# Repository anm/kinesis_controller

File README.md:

# River's Kinesis Advantage Blackpill based controller board

This is a replacement controller board for the Kinesis Advantage keyboard.
It is a development of the kinBP by https://github.com/DmNosachev.

Changes from that one:
- Added piezo sounder, allowing for key clicks / beepy tunes.
- Added connector for the original Kinesis cable. There is no need to buy extra USB cables and hack up the case!
- Removed some unneeded connectors, that were for a custom thumb board I'm not using.
- Aligned thumb connector holes properly so you can use the original cable.
- Completely rerouted.
- N.B.: The pins used for the matrix are different - you must use the correct QMK configuration, also provided on my github.

## Build Notes

- There are two options for orientation of the function key connectors. Test it works before soldering in.
- Obtain qmk keyboard files from https://github.com/anm/qmk_firmware/ river branch.
- Build QMK with `qmk flash -kb kinesis/river -km river`.
- Flash with dfu-util
- Flash: Enter bootloader by holding BOOT0 button while resetting / powering on the board, then
  `dfu-util -a 0 -d 0483:df11 -s 0x8000000:leave -D kinesis_river_blackpill411_river.bin`.
  After flashing, you can also enter the bootloader by holding both shift keys and B on the keyboard.

More info at the parent project: https://github.com/DmNosachev/kinbp

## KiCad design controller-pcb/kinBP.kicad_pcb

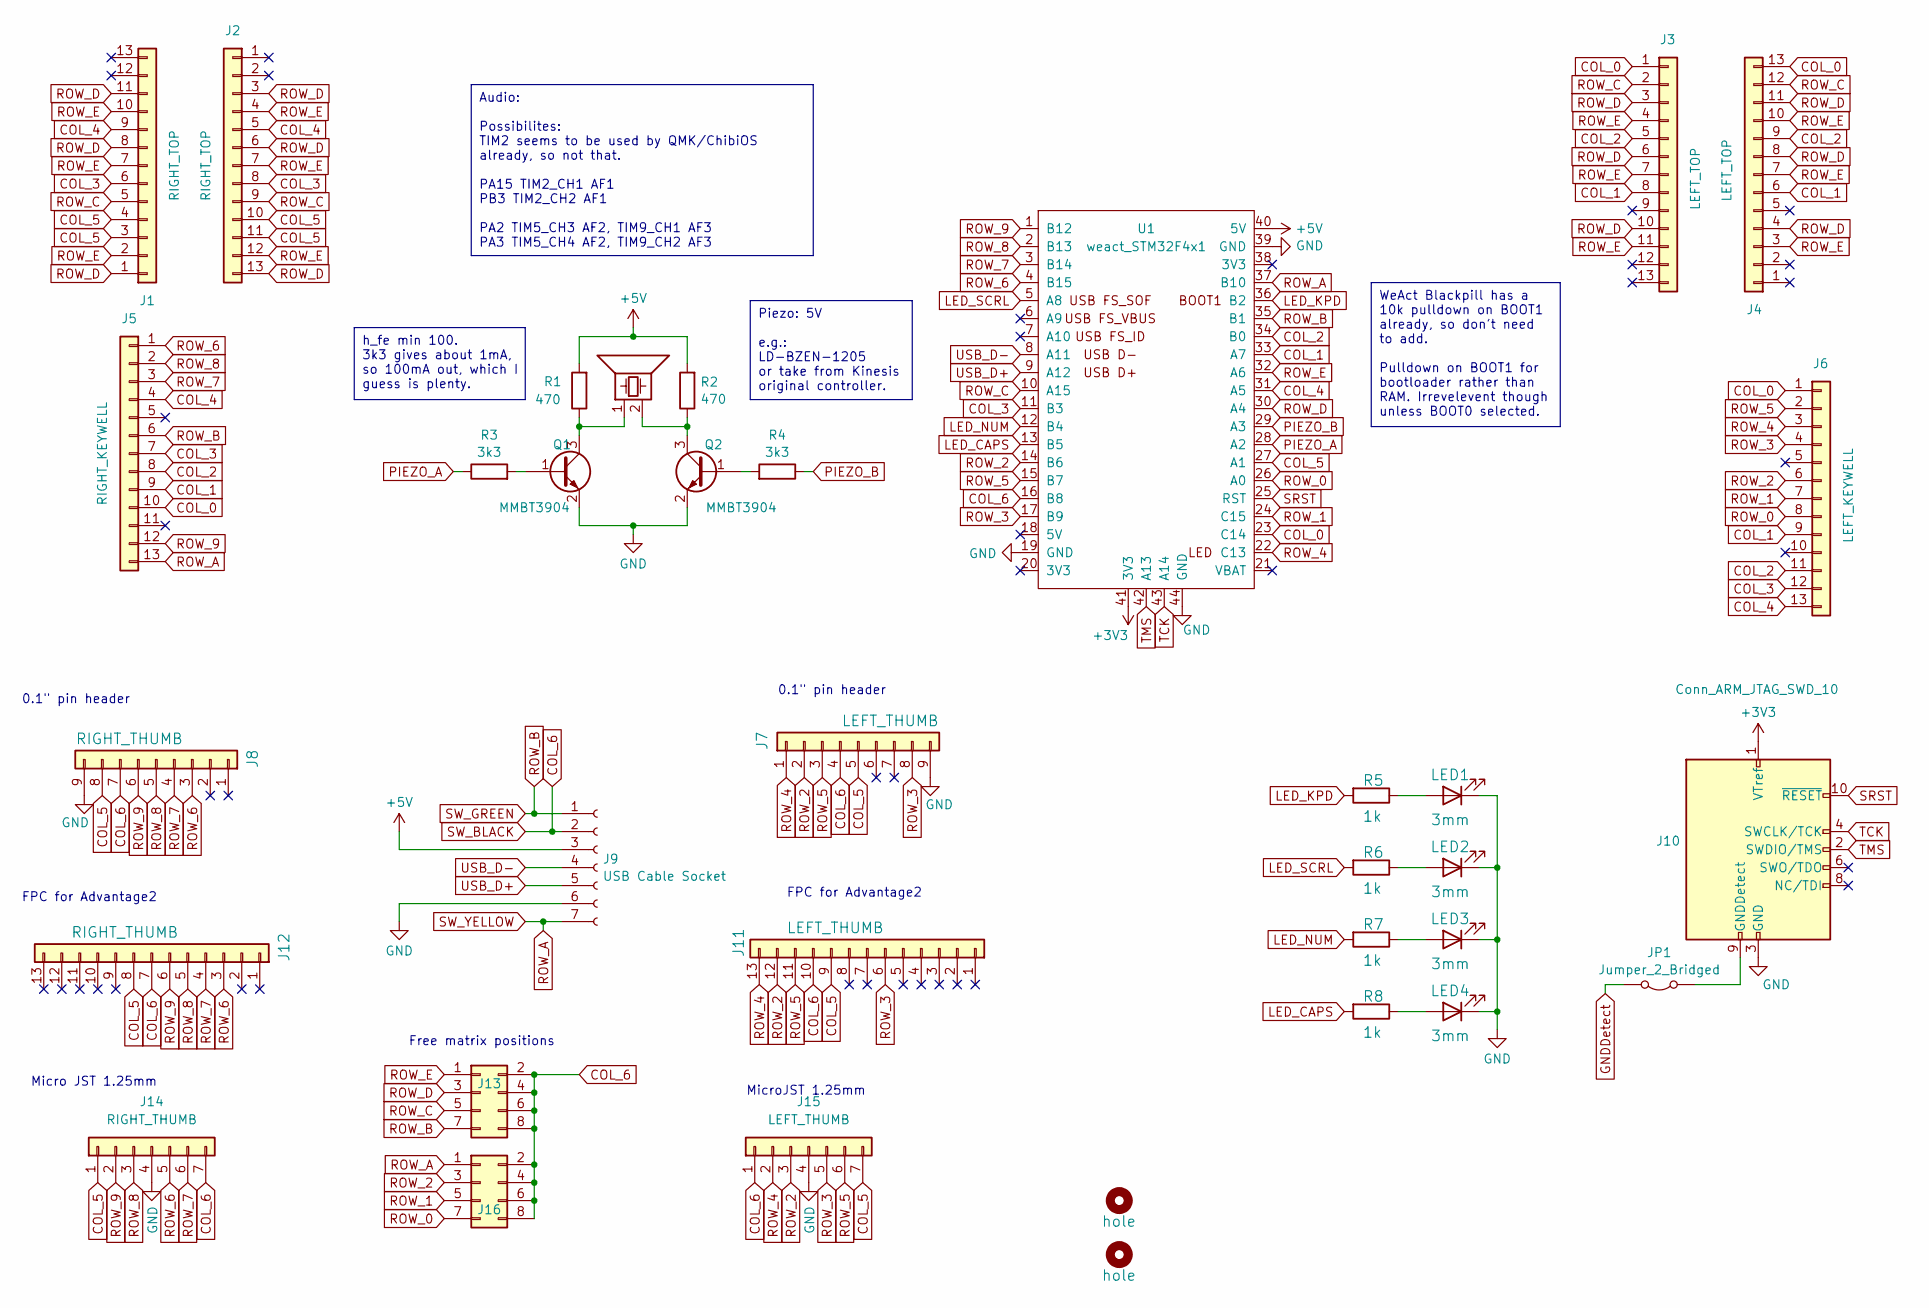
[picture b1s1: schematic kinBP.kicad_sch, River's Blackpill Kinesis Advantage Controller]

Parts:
H1: hole; MountingHole_4.3mm_M4_No_Copper
H2: hole; MountingHole_6mm
J1, J2: RIGHT_TOP; 39-53-2135
J3, J4: LEFT_TOP; 39-53-2135
J5: RIGHT_KEYWELL; 39-53-2135
J6: LEFT_KEYWELL; 39-53-2135
J7: LEFT_THUMB; PinHeader_1x09_P2.54mm_Vertical
J8: RIGHT_THUMB; PinHeader_1x09_P2.54mm_Vertical
J9: USB Cable Socket; JST_PH_B7B-PH-K_1x07_P2.00mm_Vertical
J10: Conn_ARM_JTAG_SWD_10; CONN_3220-10-0100-00_CNC; Digikey 1175-1627-ND
J11: LEFT_THUMB; 39-53-2135
J12: RIGHT_THUMB; 39-53-2135
J13, J16: Conn_02x04_Odd_Even; PinHeader_2x04_P2.54mm_Vertical
J14: RIGHT_THUMB; Molex_PicoBlade_53048-0710_1x07_P1.25mm_Horizontal
J15: LEFT_THUMB; Molex_PicoBlade_53048-0710_1x07_P1.25mm_Horizontal
JP1: Jumper_2_Bridged; SolderJumper-2_P1.3mm_Bridged2Bar_Pad1.0x1.5mm
LED1, LED2, LED3, LED4: 3mm; LED_D3.0mm_centered
LS1: LD-BZEN-1205LOUDITY; Piezos_12mm
Q1, Q2: MMBT3904; SOT-23
R1, R2: 470; R_Axial_DIN0207_L6.3mm_D2.5mm_P7.62mm_Horizontal
R3, R4: 3k3; R_Axial_DIN0207_L6.3mm_D2.5mm_P7.62mm_Horizontal
R5, R6, R7, R8: 1k; R_Axial_DIN0207_L6.3mm_D2.5mm_P7.62mm_Horizontal
U1: weact_STM32F4x1; STM32F4x1_MiniF4

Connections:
+3V3: J10.1 (VTref), U1.41 (3V3)
+5V: J9.3, R1.2, R2.2, U1.40 (5V)
COL_0: J3.1, J4.13, J5.10, J6.1, U1.23 (C14)
COL_1: J3.8, J4.6, J5.9, J6.9, U1.33 (A7)
COL_2: J3.5, J4.9, J5.8, J6.11, U1.34 (B0)
COL_3: J1.6, J2.8, J5.7, J6.12, U1.11 (B3)
COL_4: J1.9, J2.5, J5.4, J6.13, U1.31 (A5)
COL_5: J1.3, J1.4, J2.10, J2.11, J7.5, J8.8, J11.9, J12.8, J14.1, J15.7, U1.27 (A1)
COL_6: J7.4, J8.7, J9.2, J11.10, J12.7, J13.2, J13.4, J13.6, J13.8, J14.7, J15.1, J16.2, J16.4, J16.6, J16.8, U1.16 (B8)
GND: J7.9, J8.9, J9.6, J10.3 (GND), J10.5 (GND), J14.4, J15.4, LED1.1 (K), LED2.1 (K), LED3.1 (K), LED4.1 (K), Q1.2 (E), Q2.2 (E), U1.19 (GND), U1.39 (GND), U1.44 (GND)
GNDDetect: JP1.2 (B)
LED_CAPS: R8.2, U1.13 (B5)
LED_KPD: R5.2, U1.36 (B2)
LED_NUM: R7.2, U1.12 (B4)
LED_SCRL: R6.2, U1.5 (A8)
unnamed: J10.9 (GNDDetect), JP1.1 (A)
unnamed: LED1.2 (A), R5.1
unnamed: LED2.2 (A), R6.1
unnamed: LED3.2 (A), R7.1
unnamed: LED4.2 (A), R8.1
unnamed: Q1.1 (B), R3.2
unnamed: LS1.1, Q1.3 (C), R1.1
unnamed: Q2.1 (B), R4.2
unnamed: LS1.2, Q2.3 (C), R2.1
PIEZO_A: R3.1, U1.28 (A2)
PIEZO_B: R4.1, U1.29 (A3)
ROW_0: J6.8, J16.7, U1.26 (A0)
ROW_1: J6.7, J16.5, U1.24 (C15)
ROW_2: J6.6, J7.2, J11.12, J15.3, J16.3, U1.14 (B6)
ROW_3: J6.4, J7.8, J11.6, J15.5, U1.17 (B9)
ROW_4: J6.3, J7.1, J11.13, J15.2, U1.22 (C13)
ROW_5: J6.2, J7.3, J11.11, J15.6, U1.15 (B7)
ROW_6: J5.1, J8.3, J12.3, J14.5, U1.4 (B15)
ROW_7: J5.3, J8.4, J12.4, J14.6, U1.3 (B14)
ROW_8: J5.2, J8.5, J12.5, J14.3, U1.2 (B13)
ROW_9: J5.12, J8.6, J12.6, J14.2, U1.1 (B12)
ROW_A: J5.13, J9.7, J16.1, U1.37 (B10)
ROW_B: J5.6, J9.1, J13.7, U1.35 (B1)
ROW_C: J1.5, J2.9, J3.2, J4.12, J13.5, U1.10 (A15)
ROW_D: J1.1, J1.8, J1.11, J2.3, J2.6, J2.13, J3.3, J3.6, J3.10, J4.4, J4.8, J4.11, J13.3, U1.30 (A4)
ROW_E: J1.2, J1.7, J1.10, J2.4, J2.7, J2.12, J3.4, J3.7, J3.11, J4.3, J4.7, J4.10, J13.1, U1.32 (A6)
SRST: J10.10 (~RESET), U1.25 (RST)
TCK: J10.4 (SWCLK/TCK), U1.43 (A14)
TMS: J10.2 (SWDIO/TMS), U1.42 (A13)
USB_D+: J9.5, U1.9 (A12)
USB_D-: J9.4, U1.8 (A11)

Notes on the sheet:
Piezo: 5V e.g.: LD-BZEN-1205 or take from Kinesis original controller.
h_fe min 100. 3k3 gives about 1mA, so 100mA out, which I guess is plenty.
WeAct Blackpill has a 10k pulldown on BOOT1 already, so don't need to add. Pulldown on BOOT1 for bootloader rather than RAM. Irrevelevent though unless BOOT0 selected.
Audio: Possibilites: TIM2 seems to be used by QMK/ChibiOS already, so not that. PA15 TIM2_CH1 AF1 PB3 TIM2_CH2 AF1 PA2 TIM5_CH3 AF2, TIM9_CH1 AF3 PA3 TIM5_CH4 AF2, TIM9_CH2 AF3
FPC for Advantage2
0.1" pin header
MicroJST 1.25mm
Micro JST 1.25mm
Free matrix positions

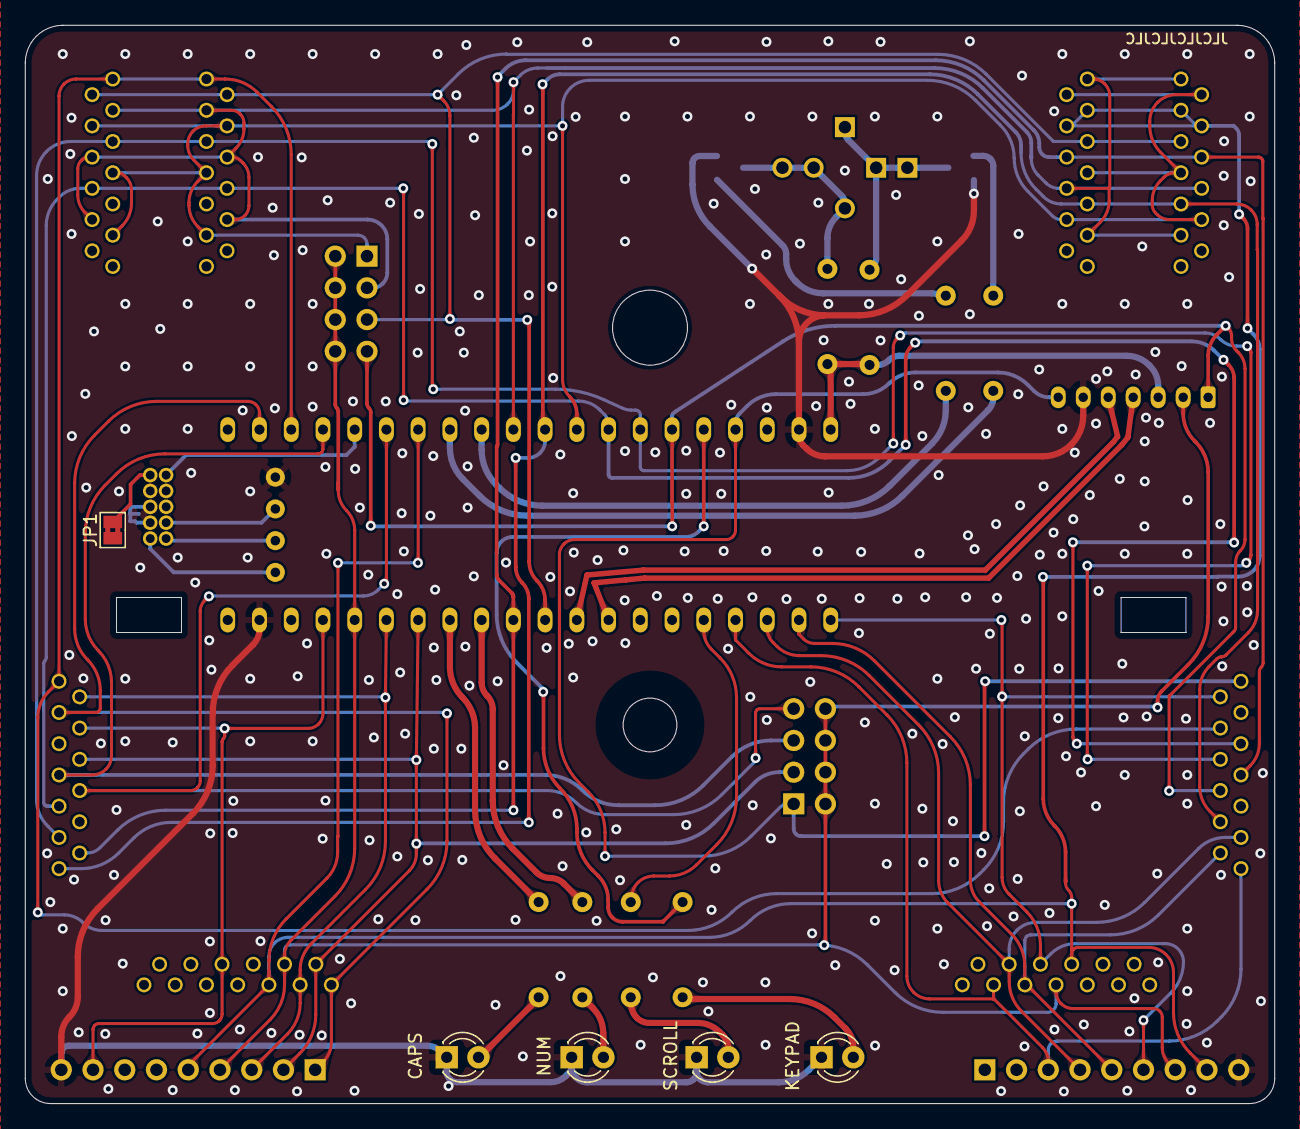
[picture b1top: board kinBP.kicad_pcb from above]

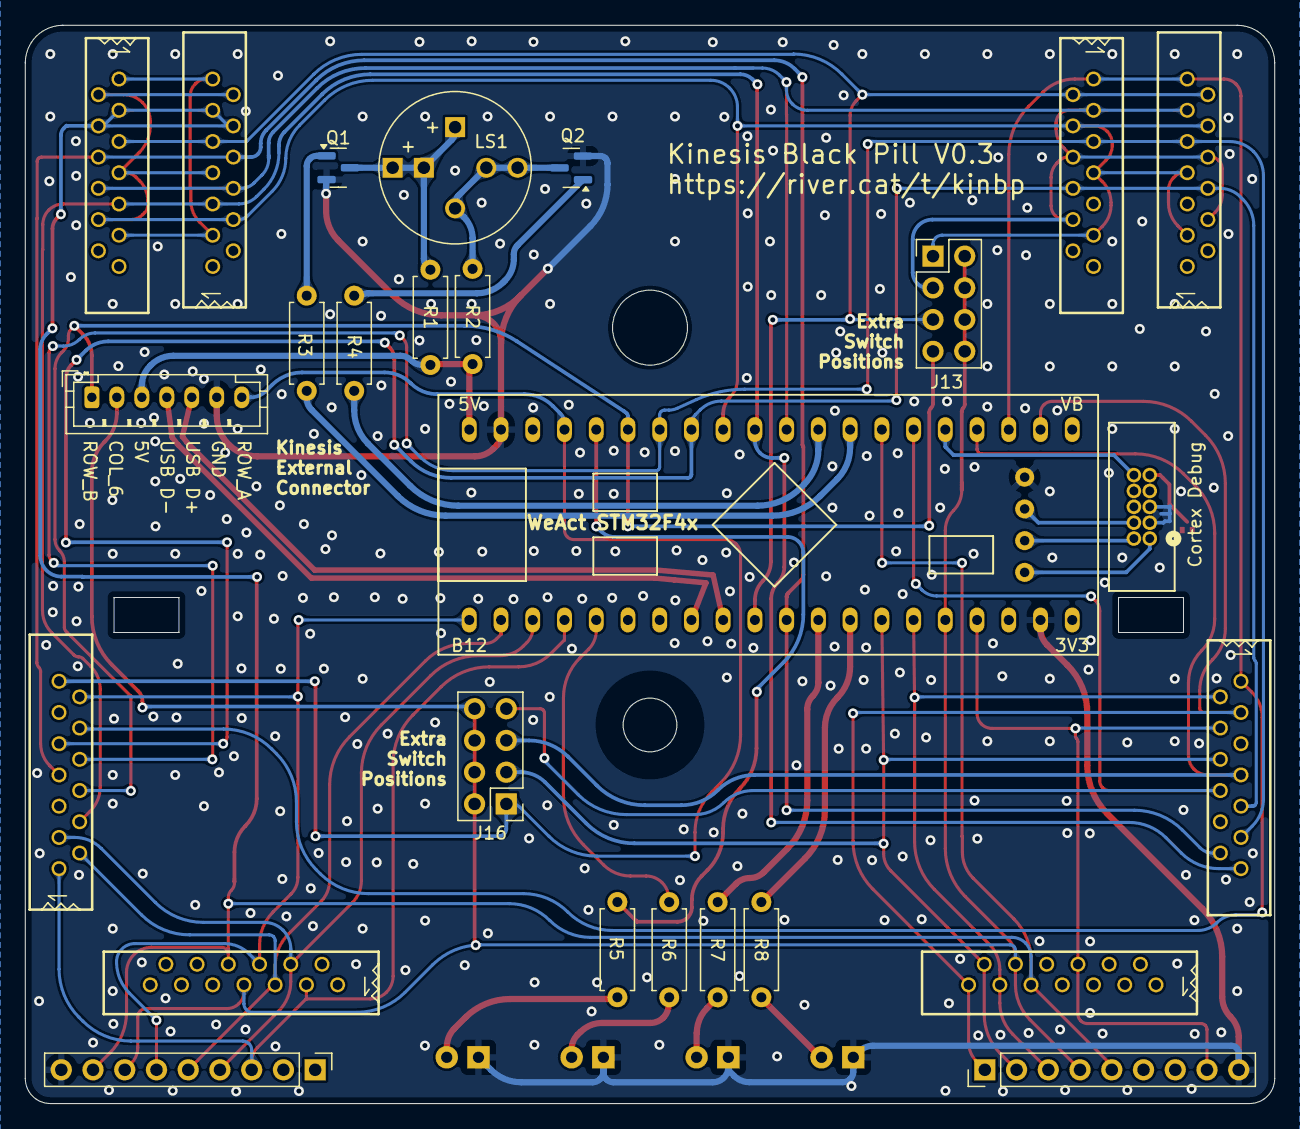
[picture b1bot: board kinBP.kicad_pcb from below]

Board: 2 copper layers, 100.0 x 86.3 mm, 33 parts (26 on the bottom side), 45 nets.

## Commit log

2024-03-06 River's modified version. Added piezo sounder. Rerouted. Split extra switch header.
2024-03-14 V0.1 as manufactured
2024-05-24 Added connector for original external USB / footpedal cable. Fixed LED positions. Prob other stuff I forgot.
2024-07-08 V0.2 as made, except then shifted screw hole down 0.2mm.
2024-07-08 Bumped version to V0.3. Added some notes, metadata.
2024-07-08 Readme
2024-07-08 Removed gerbers and thumb pcbs.
2024-07-08 Add link to my qmk branch.
2024-07-16 Added 10pin ARM Cortex debug header.
